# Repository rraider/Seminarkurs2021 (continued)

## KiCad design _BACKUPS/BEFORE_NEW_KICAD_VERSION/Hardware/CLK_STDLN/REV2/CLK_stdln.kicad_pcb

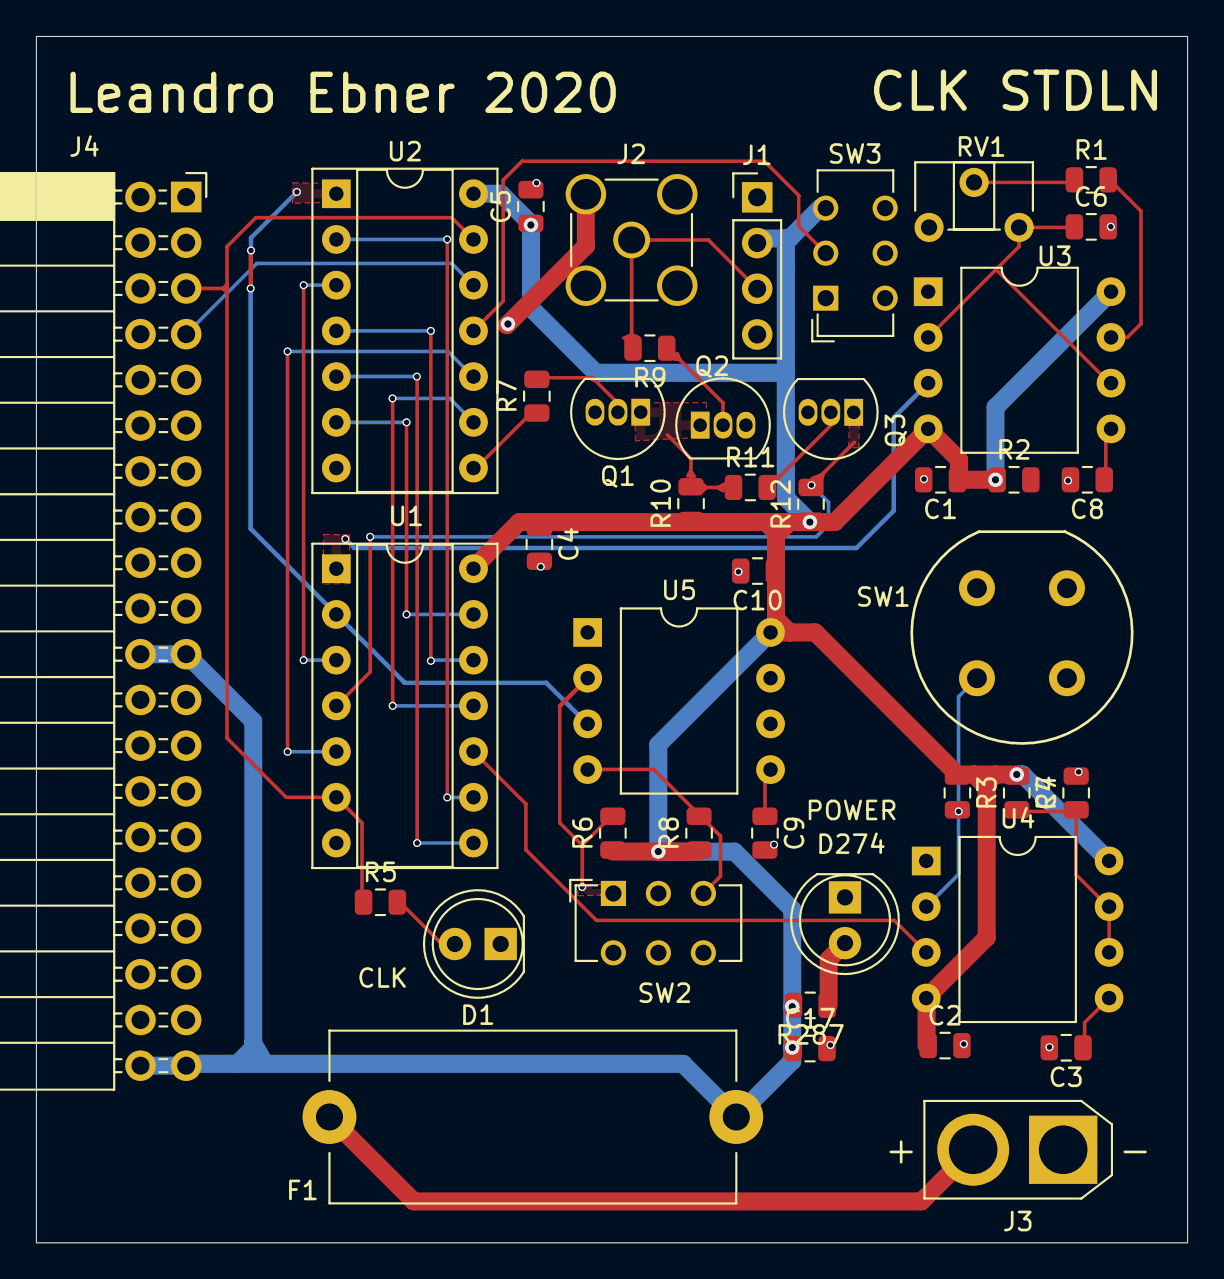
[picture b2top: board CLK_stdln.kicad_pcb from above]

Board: 2 copper layers, 63.9 x 67.0 mm, 43 parts (0 on the bottom side), 35 nets.

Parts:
C1, C2, C3, C4, C5, C7, C8, C9, C10: C; C_0805_2012Metric
C6, C17: CP; C_0805_2012Metric
D1, D274: LED; LED_D5.0mm
F1: Fuse; Fuseholder_Cylinder-5x20mm_Stelvio-Kontek_PTF78_Horizontal_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
J1: Conn_01x04_Male; PinHeader_1x04_P2.54mm_Vertical
J2: Conn_Coaxial; SMA_Amphenol_901-144_Vertical
J3: Conn_01x02; AMASS_XT30U-F_1x02_P5.0mm_Vertical
J4: Conn_02x20_Counter_Clockwise; PinSocket_2x20_P2.54mm_Horizontal
Q1, Q2, Q3: BC547; TO-92_Inline
R1, R2, R3, R4, R5, R6, R7, R8, R9, R10, R11, R12, R287: R; R_0805_2012Metric
RV1: R_POT; Potentiometer_ACP_CA6-H2,5_Horizontal
SW1: SW_Push; Push_E-Switch_KS01Q01
SW2, SW3: SW_SPDT; SW_CuK_JS202011CQN_DPDT_Straight
U1: 74LS08; DIP-14_W7.62mm_Socket
U2: 74LS04; DIP-14_W7.62mm_Socket
U3, U4, U5: NE555; DIP-8_W10.16mm

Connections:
+5V: C1.1, C2.1, C4.1, C5.1, C10.1, C17.1, F1.2, J1.2, J4.21, J4.22, J4.39, J4.40, R2.1, R3.1, R4.1, R6.1, R8.1, R10.1, R12.1, R287.2, SW3.3 (C), U1.14 (VCC), U2.14 (VCC), U3.4 (R), U3.8 (VCC), U4.4 (R), U4.8 (VCC), U5.8 (VCC)
CLK: J4.5, R5.1, U1.6, U2.13
GND: C1.2, C2.2, C3.2, C4.2, C5.2, C6.2, C7.2, C8.2, C9.2, C10.2, C17.2, D1.1 (K), D274.1 (K), J1.1, J1.4, J2.2 (Ext), J3.1, J4.1, J4.2, J4.19, J4.20, Q1.3 (E), Q2.3 (E), Q3.3 (E), SW1.1, SW2.2 (B), SW3.1 (A), U1.7 (GND), U2.7 (GND), U3.1 (GND), U4.1 (GND), U5.1 (GND), U5.6 (THR)
HLT: SW3.2 (B), U2.11
NE555A: U1.1, U3.3 (Q)
NE555B: U1.10, U4.3 (Q)
NE555C: U1.2, U2.1, U5.3 (Q)
NE555_CLK: R7.1, U2.8
unnamed: C3.1, U4.5 (CV)
unnamed: C6.1, RV1.3, U3.2 (TR), U3.6 (THR)
unnamed: C7.1, R4.2, U4.6 (THR), U4.7 (DIS)
unnamed: C8.1, U3.5 (CV)
unnamed: C9.1, U5.5 (CV)
unnamed: D1.2 (A), R5.2
unnamed: D274.2 (A), R287.1
unnamed: F1.1, J3.2
unnamed: J1.3, J2.1 (In), R9.2
unnamed: Q1.1 (C), Q2.1 (C), R10.2, R11.1
unnamed: Q1.2 (B), R7.2
unnamed: Q2.2 (B), R9.1
unnamed: Q3.1 (C), R12.2, U1.4
unnamed: Q3.2 (B), R11.2
unnamed: R1.1, RV1.2
unnamed: R1.2, U3.7 (DIS)
unnamed: R3.2, SW1.2, U4.2 (TR)
unnamed: R6.2, SW2.1 (A), U5.2 (TR)
unnamed: R8.2, SW2.3 (C), U5.4 (R)
unnamed: U1.3, U2.3
unnamed: U1.5, U2.10
unnamed: U1.8, U2.5
unnamed: U1.9, U2.2
unnamed: U1.11, U2.9
unnamed: U1.12, U2.4
unnamed: U1.13, U2.6
~CLK: J4.7, U2.12
